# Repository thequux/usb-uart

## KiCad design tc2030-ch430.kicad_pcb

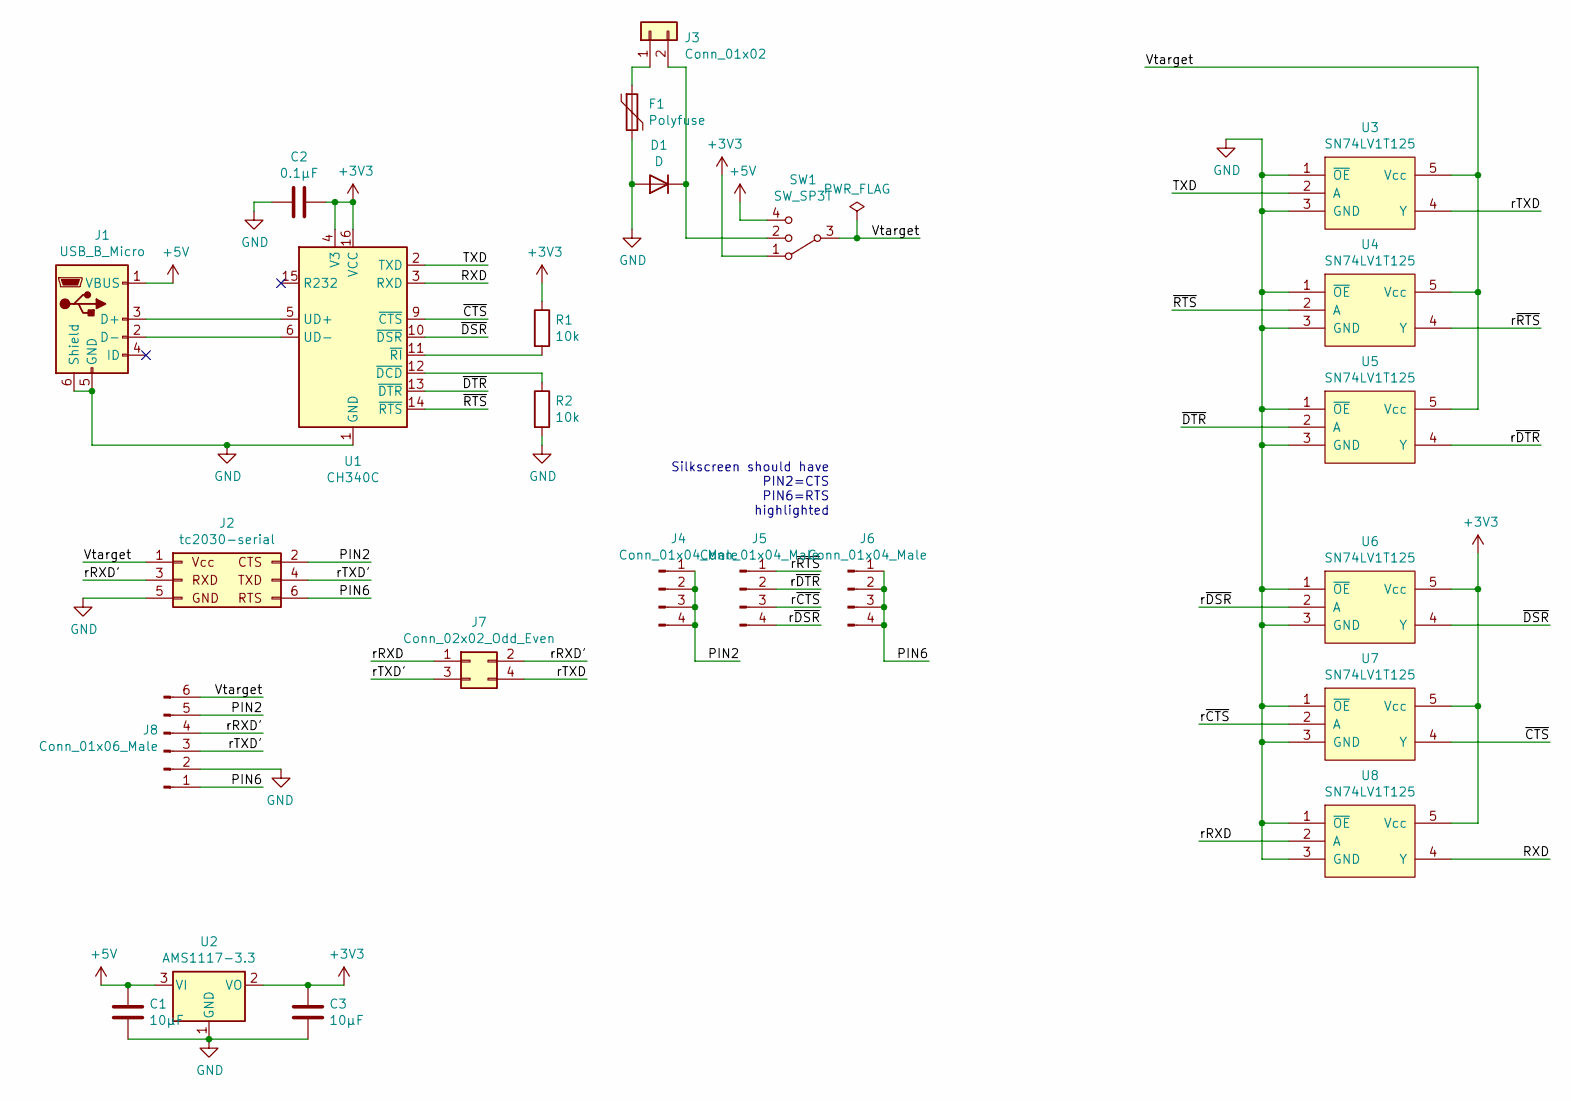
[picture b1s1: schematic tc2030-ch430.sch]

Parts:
C1, C3: 10µF; C_0805_2012Metric_Pad1.18x1.45mm_HandSolder
C2: 0.1µF; C_0805_2012Metric_Pad1.18x1.45mm_HandSolder
D1: D; D_SMA
F1: Polyfuse; Fuse_1812_4532Metric_Castellated
J1: USB_B_Micro; Jing 920-E52A2021S10100 (JLC C10418)
J2: tc2030-serial; IDC-Header_2x03_P2.54mm_Vertical
J3: Conn_01x02; PinHeader_1x02_P2.54mm_Horizontal
J4, J5, J6: Conn_01x04_Male; PinHeader_1x04_P2.54mm_Vertical
J7: Conn_02x02_Odd_Even; PinHeader_2x02_P2.54mm_Vertical
J8: Conn_01x06_Male; PinHeader_1x06_P2.54mm_Horizontal
R1, R2: 10k; R_0805_2012Metric_Pad1.20x1.40mm_HandSolder
SW1: SW_SP3T; SK13D07VG4-3PST
U1: CH340C; SOIC-16_3.9x9.9mm_P1.27mm
U2: AMS1117-3.3; SOT-223-3_TabPin2
U3, U4, U5, U6, U7, U8: SN74LV1T125; SOT-23-5_HandSoldering

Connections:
+3V3: C2.1, C3.1, R1.1, SW1.1, U1.4 (V3), U1.16 (VCC), U2.2 (VO), U6.5 (Vcc), U7.5 (Vcc), U8.5 (Vcc)
+5V: C1.1, J1.1 (VBUS), SW1.4, U2.3 (VI)
/PIN2: J2.2, J4.1, J4.2, J4.3, J4.4, J8.5
/PIN6: J2.6, J6.1, J6.2, J6.3, J6.4, J8.1
/RXD: U1.3 (RXD), U8.4 (Y)
/TXD: U1.2 (TXD), U3.2 (A)
/Vtarget: J2.1, J8.6, SW1.3, U3.5 (Vcc), U4.5 (Vcc), U5.5 (Vcc)
/rRXD: J7.1, U8.2 (A)
/rRXD': J2.3, J7.2, J8.4
/rTXD: J7.4, U3.4 (Y)
/rTXD': J2.4, J7.3, J8.3
/r~CTS: J5.3, U7.2 (A)
/r~DSR: J5.4, U6.2 (A)
/r~DTR: J5.2, U5.4 (Y)
/r~RTS: J5.1, U4.4 (Y)
/~CTS: U1.9 (~CTS), U7.4 (Y)
/~DSR: U1.10 (~DSR), U6.4 (Y)
/~DTR: U1.13 (~DTR), U5.2 (A)
/~RTS: U1.14 (~RTS), U4.2 (A)
GND: C1.2, C2.2, C3.2, D1.2 (A), F1.2, J1.5 (GND), J1.6 (Shield), J2.5, J8.2, R2.2, U1.1 (GND), U2.1 (GND), U3.1 (~OE), U3.3 (GND), U4.1 (~OE), U4.3 (GND), U5.1 (~OE), U5.3 (GND), U6.1 (~OE), U6.3 (GND), U7.1 (~OE), U7.3 (GND), U8.1 (~OE), U8.3 (GND)
unnamed: D1.1 (K), J3.2, SW1.2
unnamed: F1.1, J3.1
unnamed: J1.2 (D-), U1.6 (UD-)
unnamed: J1.3 (D+), U1.5 (UD+)
unnamed: R1.2, U1.11 (~RI)
unnamed: R2.1, U1.12 (~DCD)

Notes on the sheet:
Silkscreen should have PIN2=CTS PIN6=RTS highlighted

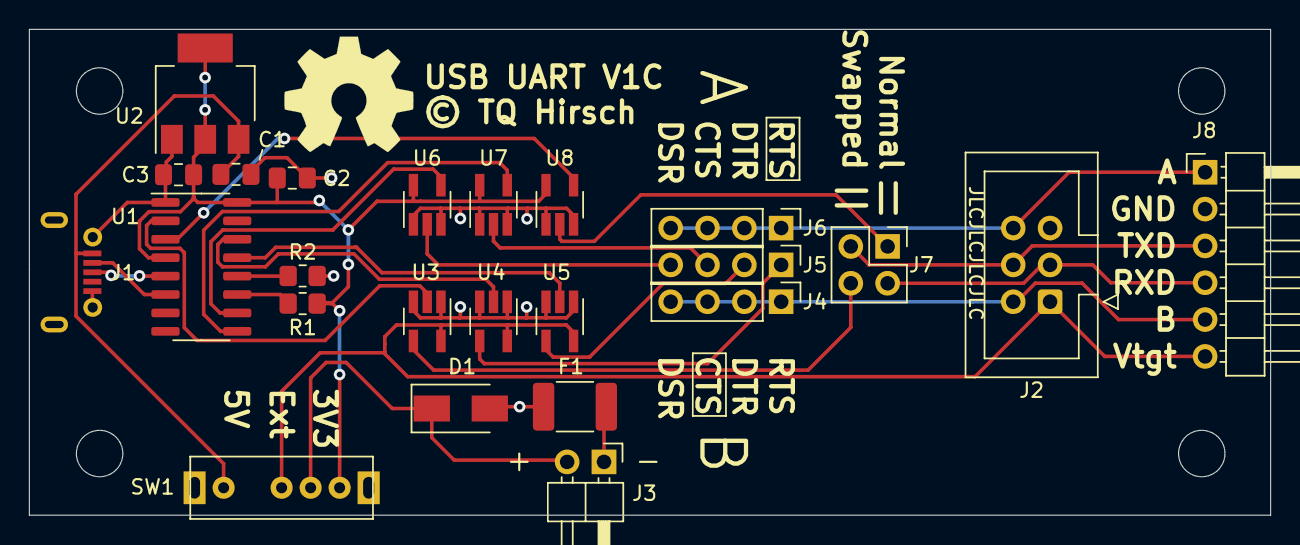
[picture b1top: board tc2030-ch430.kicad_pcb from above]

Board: 2 copper layers, 85.6 x 33.5 mm, 28 parts (0 on the bottom side), 26 nets.

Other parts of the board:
M1, M2, M3, M4: MountingHole_3.2mm_M3

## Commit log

2021-08-06 Public release

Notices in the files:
tc2030-ch430.kicad_pcb:
© TQ Hirsch
